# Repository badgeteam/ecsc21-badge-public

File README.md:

# ecsc21-badge-public
Hardware design files for the ENISA ECSC21 badge (software coming later)

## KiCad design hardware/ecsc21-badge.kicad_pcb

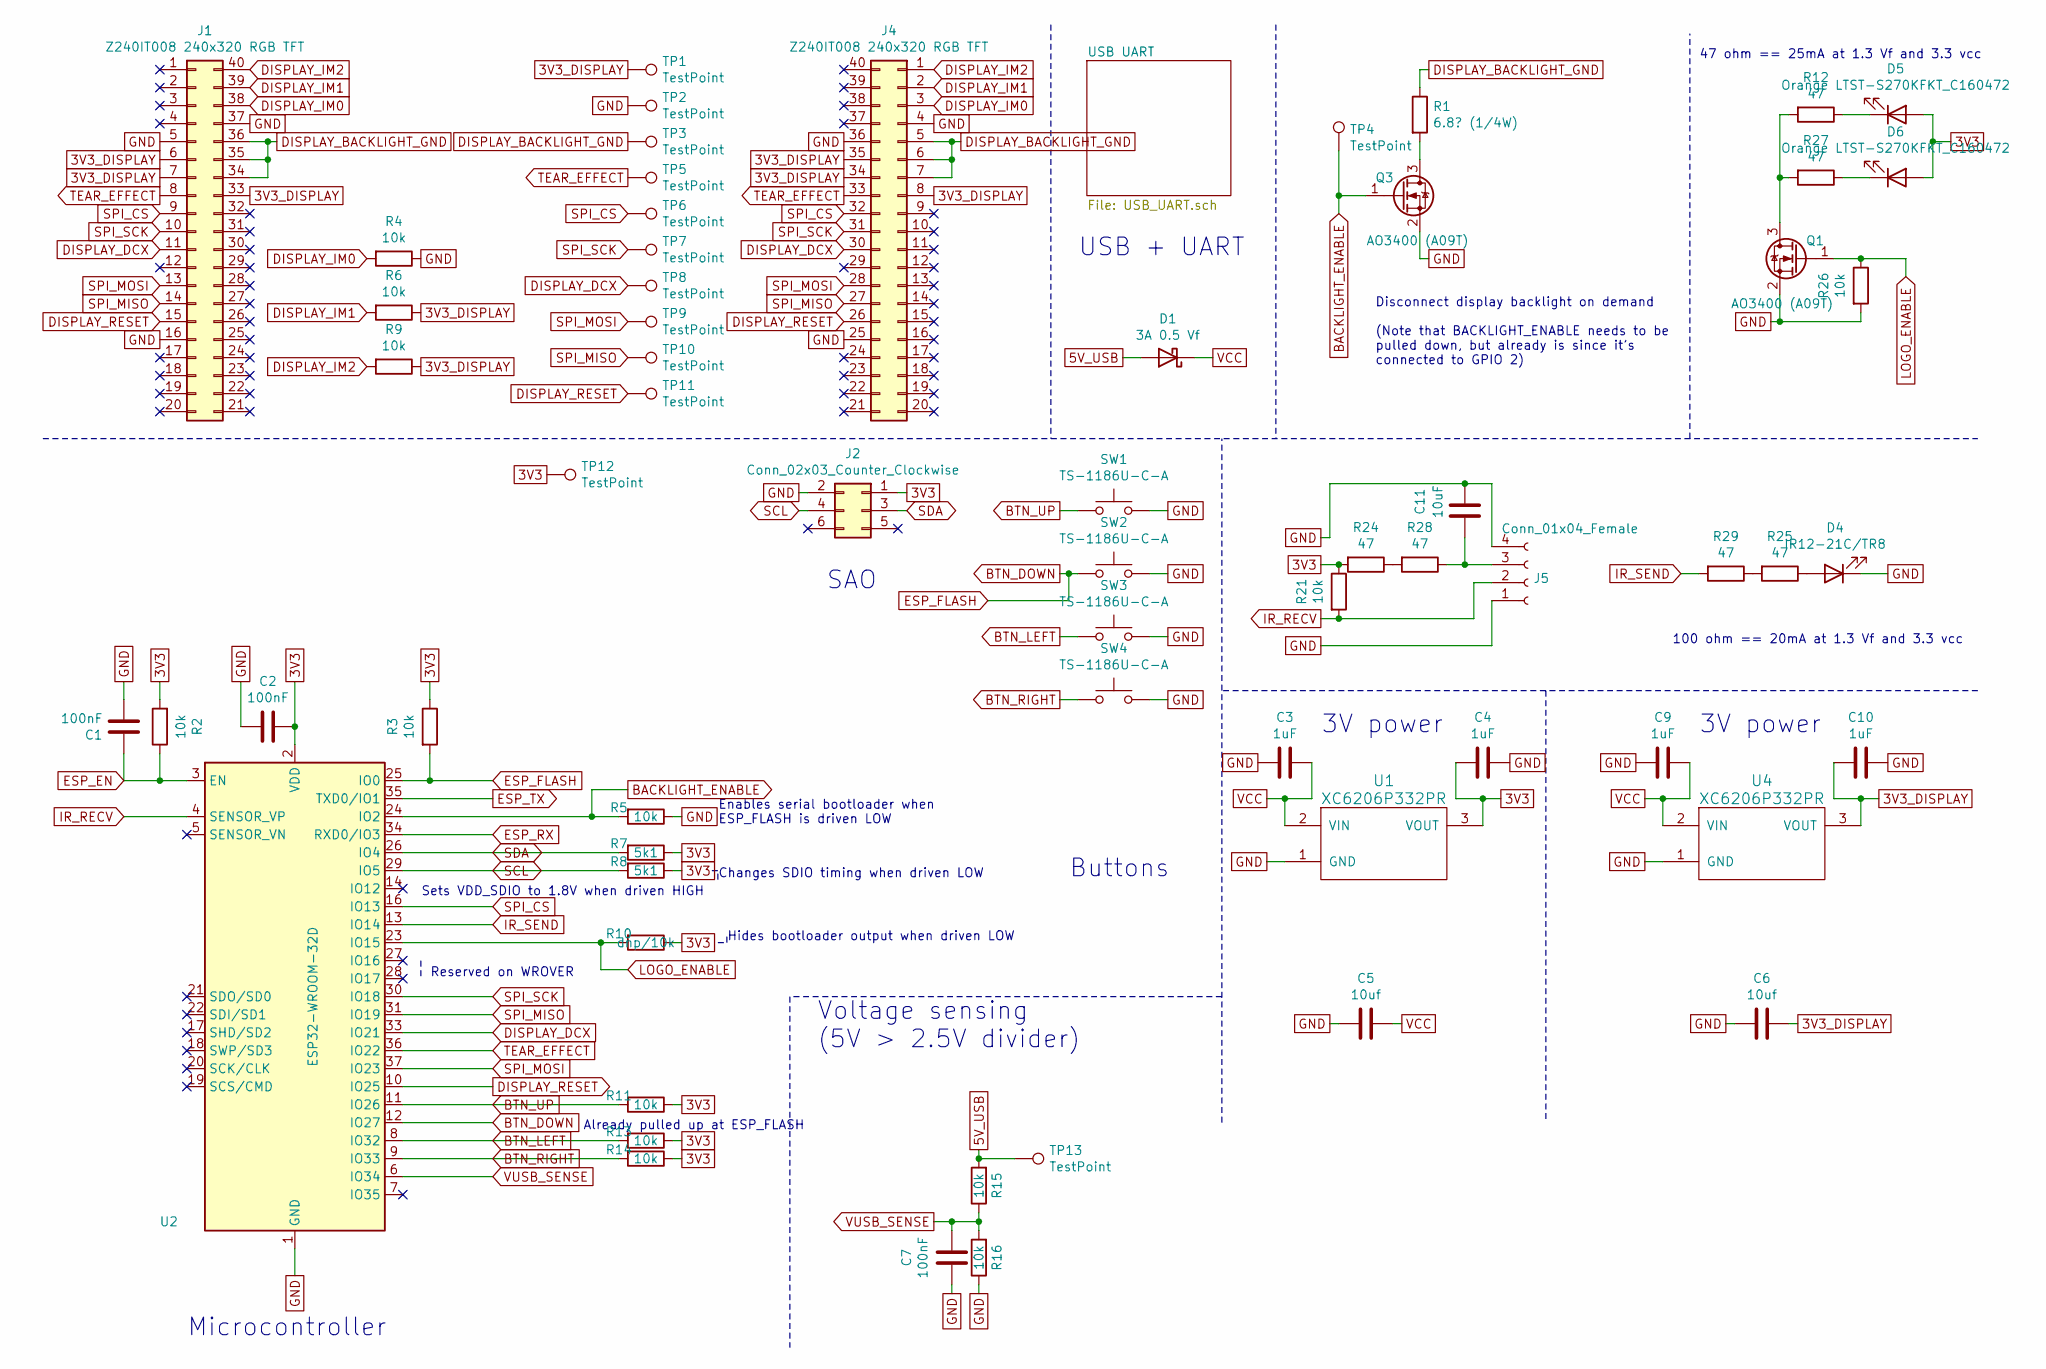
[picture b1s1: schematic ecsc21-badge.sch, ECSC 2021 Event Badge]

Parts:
C1, C2, C7: 100nF; C_0603_1608Metric
C3, C4, C9, C10: 1uF; C_0603_1608Metric
C5, C6: 10uf; C_1206_3216Metric
C11: 10uF; C_1206_3216Metric
D1: 3A 0.5 Vf; D_SMA
D4: IR12-21C/TR8; LED_1206_3216Metric
D5, D6: Orange LTST-S270KFKT_C160472; LED_0603_1608Metric
J1, J4: Z240IT008 240x320 RGB TFT; TE_4-1734839-0_1x40-1MP_P0.5mm_Horizontal
J2: Conn_02x03_Counter_Clockwise; PinSocket_2x03_P2.54mm_Vertical_SMD
J5: Conn_01x04_Female; OPTO-SMD_IRM-V840C_TR1
Q1, Q3: AO3400 (A09T); SOT-23
R1: 6.8? (1/4W); R_0805_2012Metric_Pad1.15x1.40mm_HandSolder
R2, R3, R4, R5, R6, R9, R11, R13, R14, R15, R16, R21, R26: 10k; R_0603_1608Metric
R7, R8: 5k1; R_0603_1608Metric
R10: dnp/10k; R_0603_1608Metric
R12, R24, R25, R27, R28, R29: 47; R_0603_1608Metric
SW1, SW2, SW3, SW4: TS-1186U-C-A; SW-SMD_4P-L4.7-W4.5-P1.70-LS5.5-EH
TP1, TP2, TP3, TP4, TP5, TP6, TP7, TP8, TP9, TP10, TP11, TP12, TP13: TestPoint; TestPoint_Pad_D1.5mm
U1, U4: XC6206P332PR; SOT-89-3
U2: ESP32-WROOM-32D; XCVR_ESP32-WROVER

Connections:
3V3: C2.1, C4.1, D5.2 (A), D6.2 (A), J2.1, R2.2, R3.1, R7.1, R8.1, R10.1, R11.1, R13.1, R14.1, R21.1, R24.2, TP12.1, U1.3 (VOUT), U2.2 (VDD); also elsewhere on the board
3V3_DISPLAY: C6.1, C10.1, J1.6, J1.7, J1.33, J4.8, J4.34, J4.35, R6.1, R9.1, TP1.1, U4.3 (VOUT)
5V_USB: D1.2 (A), R15.2, TP13.1; also elsewhere on the board
BACKLIGHT_ENABLE: Q3.1 (G), R5.2, TP4.1, U2.24 (IO2)
BTN_DOWN: R3.2, SW2.1, U2.12 (IO27), U2.25 (IO0); also elsewhere on the board
BTN_LEFT: R13.2, SW3.1, U2.8 (IO32)
BTN_RIGHT: R14.2, SW4.1, U2.9 (IO33)
BTN_UP: R11.2, SW1.1, U2.11 (IO26)
DISPLAY_BACKLIGHT_GND: J1.34, J1.35, J1.36, J4.5, J4.6, J4.7, R1.1, TP3.1
DISPLAY_DCX: J1.11, J4.30, TP8.1, U2.33 (IO21)
DISPLAY_IM0: J1.38, J4.3, R4.2
DISPLAY_IM1: J1.39, J4.2, R6.2
DISPLAY_IM2: J1.40, J4.1, R9.2
DISPLAY_RESET: J1.15, J4.26, TP11.1, U2.10 (IO25)
ESP_EN: C1.1, R2.1, U2.3 (EN); also elsewhere on the board
ESP_RX: U2.34 (RXD0/IO3); also elsewhere on the board
ESP_TX: U2.35 (TXD0/IO1); also elsewhere on the board
GND: C1.2, C2.2, C3.1, C4.2, C5.2, C6.2, C7.2, C9.1, C10.2, C11.1, D4.1 (K), J1.5, J1.16, J1.37, J2.2, J4.4, J4.25, J4.36, J5.1, J5.4, Q1.2 (S), Q3.2 (S), R4.1, R5.1, R16.1, R26.2, SW1.2, SW2.2, SW3.2, SW4.2, TP2.1, U1.1 (GND), U2.1 (GND), U2.15 (GND), U2.38 (GND), U2.39 (GND), U4.1 (GND); also elsewhere on the board
IR_RECV: J5.2, R21.2, U2.4 (SENSOR_VP)
IR_SEND: R29.2, U2.13 (IO14)
LOGO_ENABLE: Q1.1 (G), R10.2, R26.1, U2.23 (IO15)
unnamed: C11.2, J5.3, R28.1
unnamed: D4.2 (A), R25.1
unnamed: D5.1 (K), R12.1
unnamed: D6.1 (K), R27.1
unnamed: Q1.3 (D), R12.2, R27.2
unnamed: Q3.3 (D), R1.2
unnamed: R24.1, R28.2
unnamed: R25.2, R29.1
SCL: J2.4, R8.2, U2.29 (IO5)
SDA: J2.3, R7.2, U2.26 (IO4)
SPI_CS: J1.9, J4.32, TP6.1, U2.16 (IO13)
SPI_MISO: J1.14, J4.27, TP10.1, U2.31 (IO19)
SPI_MOSI: J1.13, J4.28, TP9.1, U2.37 (IO23)
SPI_SCK: J1.10, J4.31, TP7.1, U2.30 (IO18)
TEAR_EFFECT: J1.8, J4.33, TP5.1, U2.36 (IO22)
VCC: C3.2, C5.1, C9.2, D1.1 (K), U1.2 (VIN), U4.2 (VIN)
VUSB_SENSE: C7.1, R15.1, R16.2, U2.6 (IO34)

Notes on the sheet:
Hides bootloader output when driven LOW
Changes SDIO timing when driven LOW
Enables serial bootloader when ESP_FLASH is driven LOW
USB + UART
3V power
Microcontroller
Voltage sensing (5V > 2.5V divider)
Disconnect display backlight on demand (Note that BACKLIGHT_ENABLE needs to be pulled down, but already is since it’s connected to GPIO 2)
SAO
Buttons
Sets VDD_SDIO to 1.8V when driven HIGH
Reserved on WROVER
Already pulled up at ESP_FLASH
100 ohm == 20mA at 1.3 Vf and 3.3 vcc
47 ohm == 25mA at 1.3 Vf and 3.3 vcc

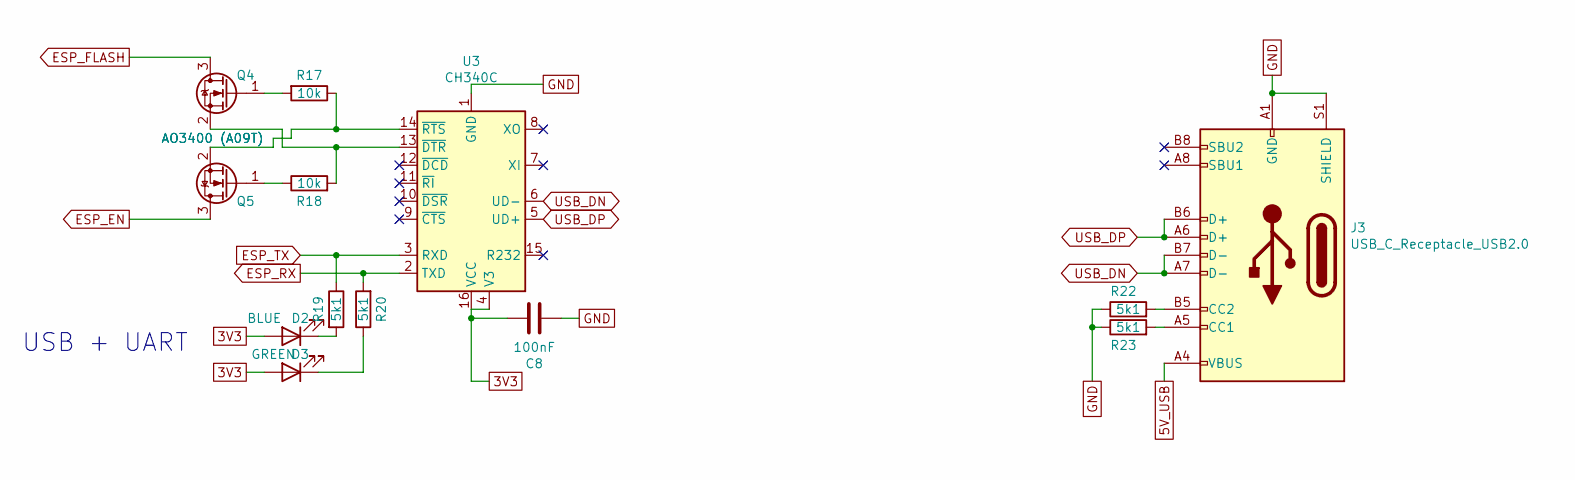
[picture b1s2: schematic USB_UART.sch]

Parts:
C8: 100nF; C_0603_1608Metric
D2: BLUE; LED_0603_1608Metric
D3: GREEN; LED_0603_1608Metric
J3: USB_C_Receptacle_USB2.0; USB_C_Receptacle_China_SMT
Q4, Q5: AO3400 (A09T); SOT-23
R17, R18: 10k; R_0603_1608Metric
R19, R20, R22, R23: 5k1; R_0603_1608Metric
U3: CH340C; SOIC-16_3.9x9.9mm_P1.27mm

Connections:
3V3: C8.2, D2.2 (A), D3.2 (A), U3.4 (V3), U3.16 (VCC); also elsewhere on the board
5V_USB: J3.A4 (VBUS), J3.A9 (VBUS), J3.B4 (VBUS), J3.B9 (VBUS); also elsewhere on the board
BTN_DOWN: Q4.3 (D); also elsewhere on the board
ESP_EN: Q5.3 (D); also elsewhere on the board
ESP_RX: R20.2, U3.2 (TXD); also elsewhere on the board
ESP_TX: R19.1, U3.3 (RXD); also elsewhere on the board
GND: C8.1, J3.A1 (GND), J3.A12 (GND), J3.B1 (GND), J3.B12 (GND), J3.S1 (SHIELD), R22.1, R23.1, U3.1 (GND); also elsewhere on the board
unnamed: D2.1 (K), R19.2
unnamed: D3.1 (K), R20.1
unnamed: J3.A5 (CC1), R23.2
unnamed: J3.B5 (CC2), R22.2
unnamed: Q4.1 (G), R17.2
unnamed: Q4.2 (S), R18.2, U3.13 (~DTR)
unnamed: Q5.1 (G), R18.1
unnamed: Q5.2 (S), R17.1, U3.14 (~RTS)
USB_DN: J3.A7 (D-), J3.B7 (D-), U3.6 (UD-)
USB_DP: J3.A6 (D+), J3.B6 (D+), U3.5 (UD+)

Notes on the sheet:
USB + UART

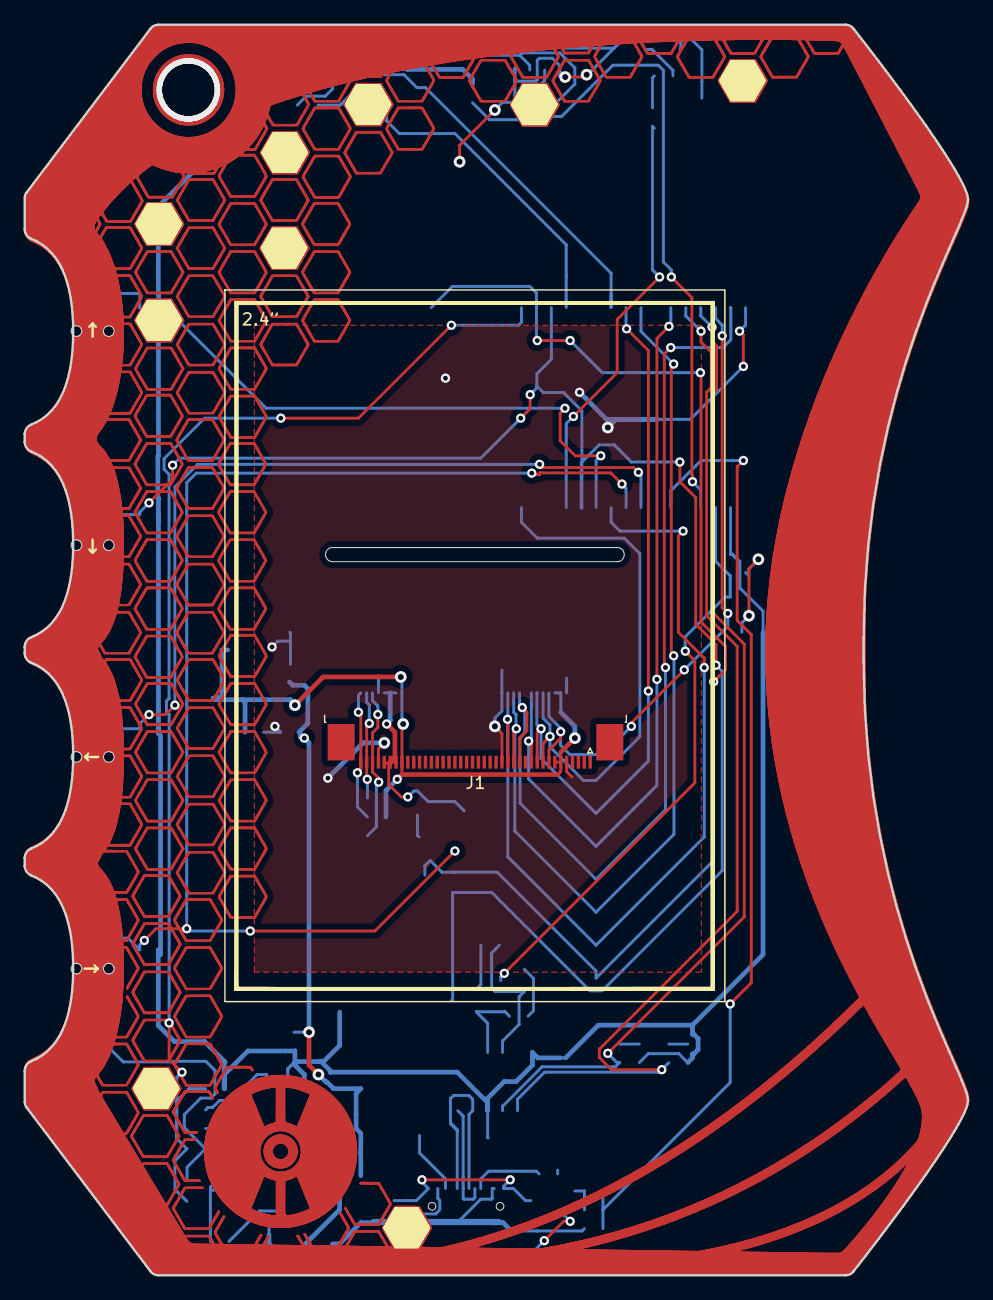
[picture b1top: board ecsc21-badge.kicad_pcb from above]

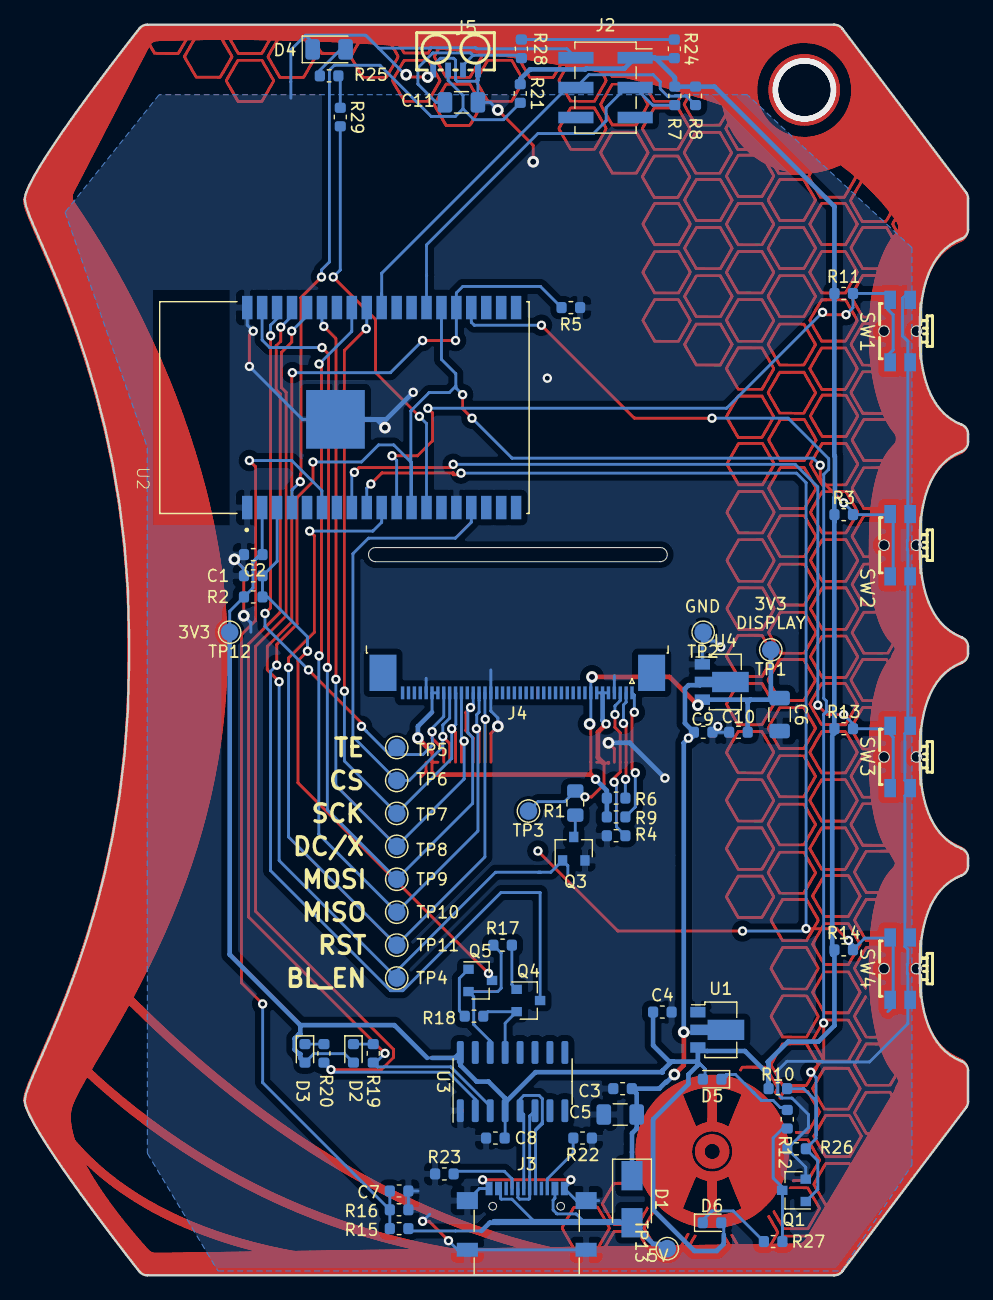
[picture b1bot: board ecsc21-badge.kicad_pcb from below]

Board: 2 copper layers, 80.2 x 106.3 mm, 76 parts (75 on the bottom side), 48 nets.

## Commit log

2021-10-22 Open sourced hardware for ECSC2021 badge
